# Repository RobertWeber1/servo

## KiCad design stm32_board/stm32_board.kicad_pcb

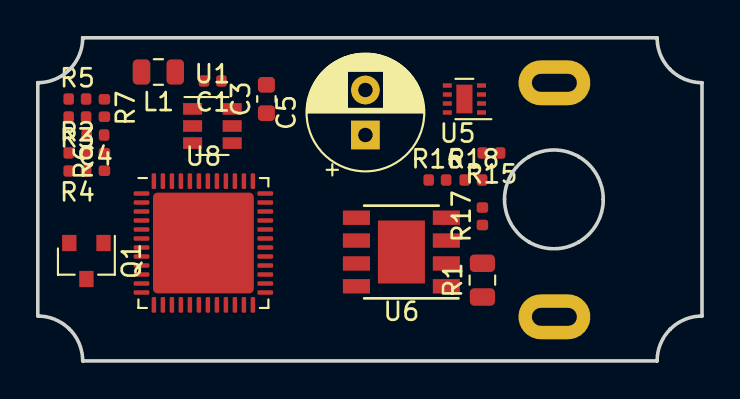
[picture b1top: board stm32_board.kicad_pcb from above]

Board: 2 copper layers, 36.9 x 18.0 mm, 22 parts (0 on the bottom side), 17 nets, no tracks yet.

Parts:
C1: 0402_100nF__104_10%_16V; C_0402_1005Metric
C3: 0603_4.7uF__475_10%_16V; C_0603_1608Metric
C4: 0402_33pF__330_5%_50V; C_0402_1005Metric
C5: 3528_100uF__107_10%_6.3V; CP_Radial_D6.3mm_P2.50mm
L1: 0805_2.2uH_10%; L_0805_2012Metric
O1: Outline
Q1: AO3401A; SOT-23
R1: 0,01; R_0805_2012Metric
R2: 0402_8.2KΩ__8201_1%; R_0402_1005Metric
R3: 0402_120KΩ__1203_1%; R_0402_1005Metric
R4: 0402_470Ω__4700_1%; R_0402_1005Metric
R5, R7: 0402_2KΩ__2001_1%; R_0402_1005Metric
R6: 0402_200Ω__2000_1%; R_0402_1005Metric
R15, R17: 0402_100KΩ__1003_1%; R_0402_1005Metric
R16, R18: R_Small; R_0402_1005Metric
U1: MP2451DT-LF-Z_[C14123]; SOT-23-6
U5: DRV8837; WSON-8-1EP_2x2mm_P0.5mm_EP0.9x1.6mm
U6: MAX9918A; Diodes_SO-8EP
U8: STM32F072C8Ux; QFN-48-1EP_7x7mm_P0.5mm_EP5.6x5.6mm

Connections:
+3V3: C4.1, L1.2, R7.2, R15.1, U5.8, U6.5
+5V: C3.1, Q1.2, U1.5
/M(+): R1.2, U5.2, U6.2
/M+: O1.2, R1.1, U6.1
/M-: O1.1, U5.3
/MOTOR_CURRENT: R18.2, U6.8
/VM: C5.1, U5.1
GND: C3.2, C5.2, Q1.1, R6.1, R17.2, U1.2, U5.4, U5.9, U6.4
unnamed: C1.1, L1.1, U1.6
unnamed: C1.2, U1.1
unnamed: C4.2, R2.2, R3.1, U1.3
unnamed: R2.1, R4.2
unnamed: R3.2, R5.1
unnamed: R4.1, R6.2
unnamed: R5.2, R7.1
unnamed: R15.2, R16.1, R17.1, U6.6
unnamed: R16.2, R18.1, U6.7
